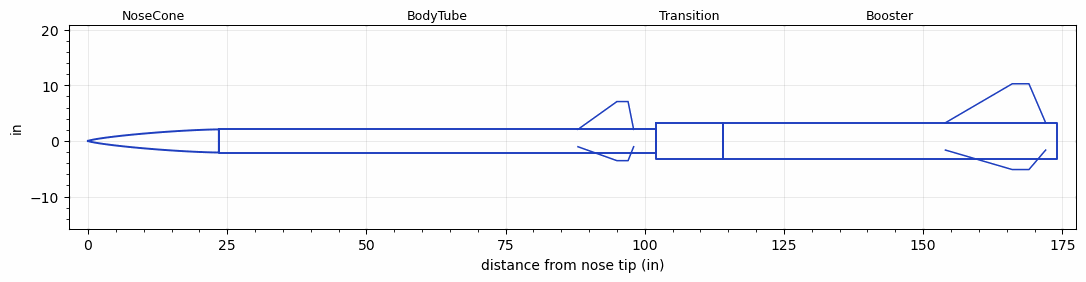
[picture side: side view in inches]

<RASAeroDocument>
 <FileVersion>2</FileVersion>
 <RocketDesign>
  <NoseCone>
   <Length>23.5</Length>
   <Diameter>4.1534</Diameter>
   <Shape>Von Karman Ogive</Shape>
   <BluntRadius>0.0625</BluntRadius>
   <Location>0</Location>
  </NoseCone>
  <BodyTube>
   <Length>78.5</Length>
   <Diameter>4.1534</Diameter>
   <Location>23.5</Location>
   <Fin>
    <Count>3</Count>
    <Chord>10</Chord>
    <Span>5</Span>
    <SweepDistance>7</SweepDistance>
    <TipChord>2</TipChord>
    <Thickness>0.1875</Thickness>
    <LERadius>0.0313</LERadius>
    <Location>14</Location>
    <AirfoilSection>Hexagonal</AirfoilSection>
    <FX1>0.86</FX1>
    <FX3>0.51</FX3>
   </Fin>
  </BodyTube>
  <Transition>
   <Length>12</Length>
   <Diameter>6.54</Diameter>
   <Location>102</Location>
   <RearDiameter>6.54</RearDiameter>
  </Transition>
  <Booster>
   <Length>60</Length>
   <Diameter>6.54</Diameter>
   <InsideDiameter>6.54</InsideDiameter>
   <Location>114</Location>
   <ShoulderLength>0</ShoulderLength>
   <Fin>
    <Count>3</Count>
    <Chord>18</Chord>
    <Span>7</Span>
    <SweepDistance>12</SweepDistance>
    <TipChord>3</TipChord>
    <Thickness>0.1875</Thickness>
    <LERadius>0.0313</LERadius>
    <Location>20</Location>
    <AirfoilSection>Hexagonal</AirfoilSection>
    <FX1>0.992</FX1>
    <FX3>0.544</FX3>
   </Fin>
  </Booster>
  <Surface>Rough Camouflage Paint</Surface>
  <ModifiedBarrowman>True</ModifiedBarrowman>
  <Turbulence>True</Turbulence>
  <UseBooster1>False</UseBooster1>
  <UseBooster2>False</UseBooster2>
 </RocketDesign>
 <LaunchSite>
  <Altitude>3500</Altitude>
  <Pressure>0</Pressure>
  <RodAngle>2</RodAngle>
  <RodLength>18</RodLength>
  <Temperature>80</Temperature>
  <WindSpeed>10</WindSpeed>
 </LaunchSite>
 <Recovery>
  <Altitude1>1000</Altitude1>
  <Altitude2>1000</Altitude2>
  <DeviceType1>None</DeviceType1>
  <DeviceType2>None</DeviceType2>
  <Event1>False</Event1>
  <Event2>False</Event2>
  <Size1>1</Size1>
  <Size2>1</Size2>
  <EventType1>None</EventType1>
  <EventType2>None</EventType2>
  <CD1>1.33</CD1>
  <CD2>1.33</CD2>
 </Recovery>
 <SimulationList>
  <Simulation>
   <SustainerEngine>BERMA-25000-02  (Karman_AIAA-capstone)</SustainerEngine>
   <SustainerLaunchWt>45.69</SustainerLaunchWt>
   <SustainerNozzleDiameter>3.93</SustainerNozzleDiameter>
   <SustainerCG>72</SustainerCG>
   <SustainerIgnitionDelay>8</SustainerIgnitionDelay>
   <Booster1Engine>O8000  (CTI)</Booster1Engine>
   <Booster1LaunchWt>142.46</Booster1LaunchWt>
   <Booster1SeparationDelay>0</Booster1SeparationDelay>
   <Booster1IgnitionDelay>0</Booster1IgnitionDelay>
   <Booster1CG>117</Booster1CG>
   <Booster1NozzleDiameter>4.25</Booster1NozzleDiameter>
   <IncludeBooster1>True</IncludeBooster1>
   <Booster2Delay>0</Booster2Delay>
   <IncludeBooster2>False</IncludeBooster2>
   <TimetoApogee>168.7494</TimetoApogee>
   <MaxAltitude>406526.4</MaxAltitude>
   <MaxVelocity>6164.229</MaxVelocity>
   <OptimumWt>28.83266</OptimumWt>
   <OptimumMaxAlt>28.83266</OptimumMaxAlt>
  </Simulation>
  <Simulation>
   <SustainerEngine>BERMA-25000-02  (Karman_AIAA-capstone)</SustainerEngine>
   <SustainerLaunchWt>28</SustainerLaunchWt>
   <SustainerNozzleDiameter>4</SustainerNozzleDiameter>
   <SustainerCG>70</SustainerCG>
   <SustainerIgnitionDelay>24</SustainerIgnitionDelay>
   <Booster1Engine>O8000  (CTI)</Booster1Engine>
   <Booster1LaunchWt>132</Booster1LaunchWt>
   <Booster1SeparationDelay>0</Booster1SeparationDelay>
   <Booster1IgnitionDelay>0</Booster1IgnitionDelay>
   <Booster1CG>126</Booster1CG>
   <Booster1NozzleDiameter>6</Booster1NozzleDiameter>
   <IncludeBooster1>True</IncludeBooster1>
   <Booster2Delay>0</Booster2Delay>
   <IncludeBooster2>False</IncludeBooster2>
   <TimetoApogee>37.12066</TimetoApogee>
   <MaxAltitude>95524.92</MaxAltitude>
   <MaxVelocity>21794.59</MaxVelocity>
   <OptimumWt>31.35938</OptimumWt>
   <OptimumMaxAlt>31.35938</OptimumMaxAlt>
  </Simulation>
 </SimulationList>
</RASAeroDocument>
